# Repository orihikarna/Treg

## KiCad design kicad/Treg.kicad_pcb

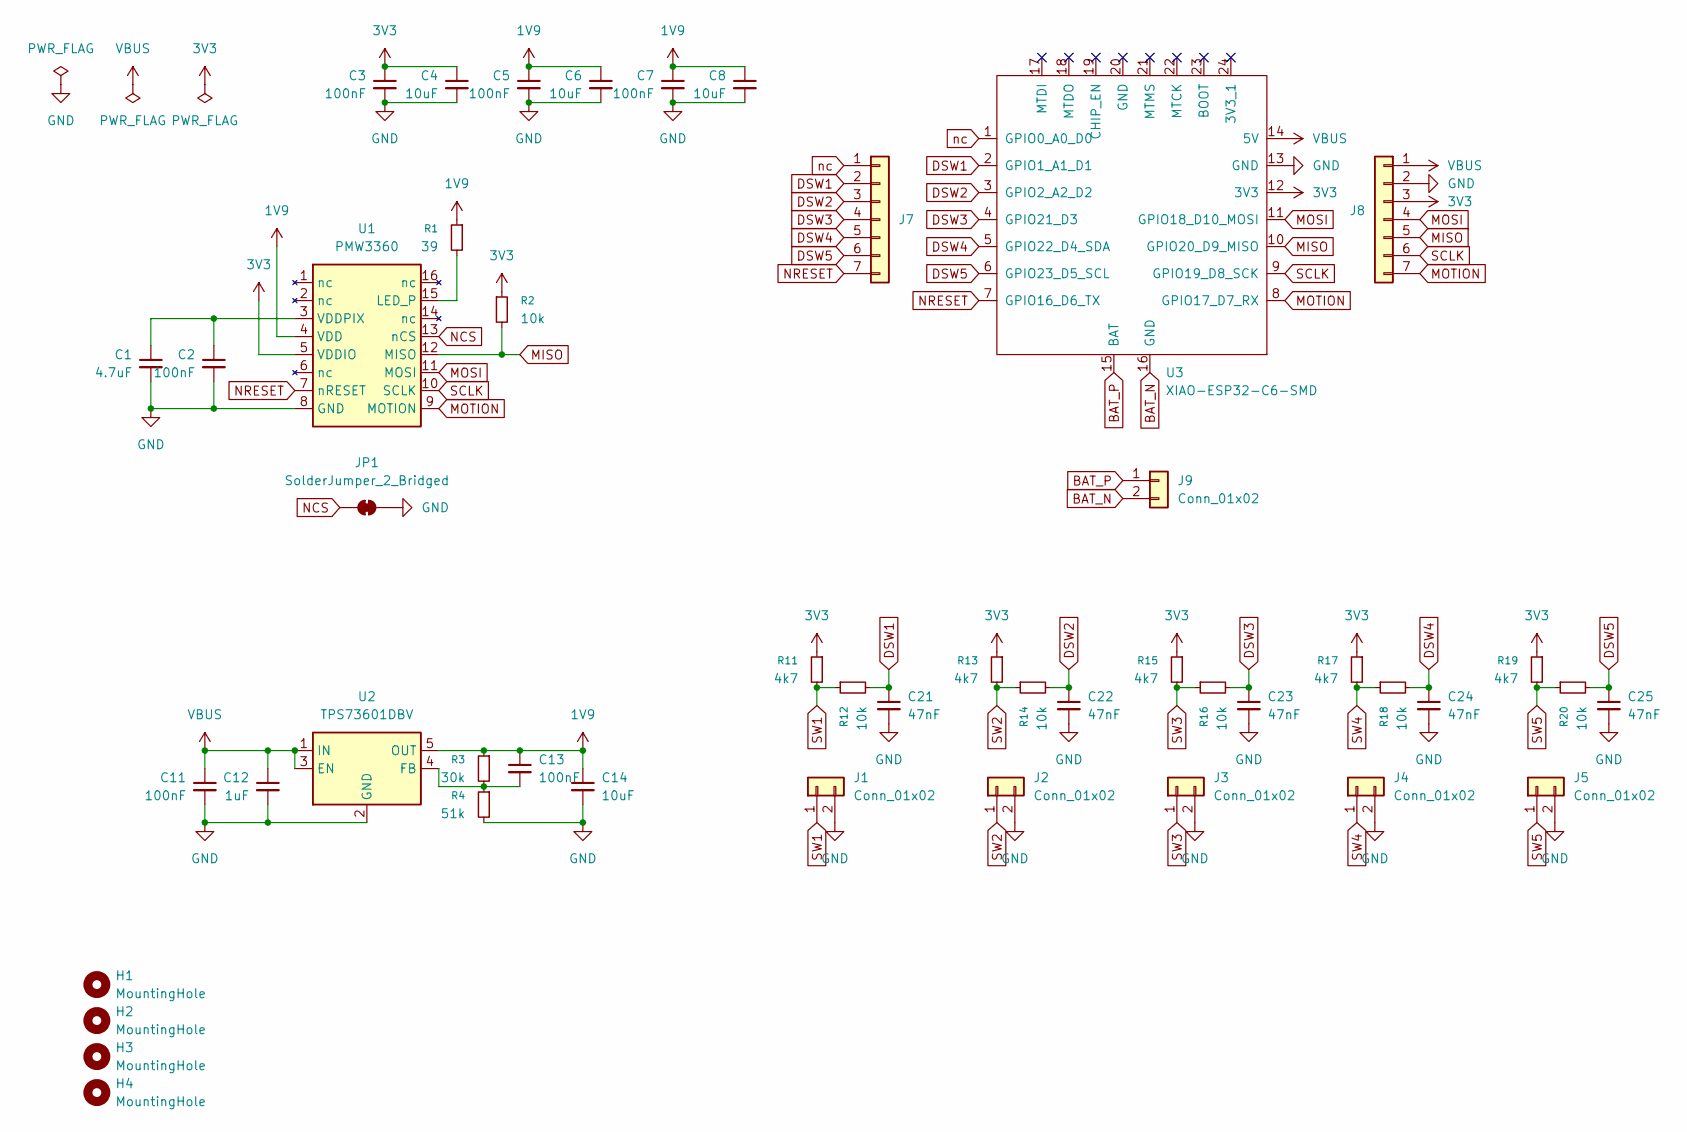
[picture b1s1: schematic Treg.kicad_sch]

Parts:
C1: 4.7uF; C_0603_1608Metric
C2, C3, C5, C7, C11, C13: 100nF; C_0603_1608Metric
C4, C6, C8, C14: 10uF; C_0603_1608Metric
C12: 1uF; C_0603_1608Metric
C21, C22, C23, C24, C25: 47nF; C_0603_1608Metric
H1, H2, H3, H4: MountingHole; MountingHole_2.2mm_M2
J1, J2, J3, J4, J5: Conn_01x02; PinHeader_1x02_P2.54mm_Vertical
J7, J8: Conn_01x07; PinHeader_1x07_P2.54mm_Vertical
J9: Conn_01x02; BatJumper
JP1: SolderJumper_2_Bridged; SolderJumper-2_P1.3mm_Bridged_RoundedPad1.0x1.5mm
R1: 39; R_0603_1608Metric_Pad0.98x0.95mm_HandSolder
R2, R12, R14, R16, R18, R20: 10k; R_0603_1608Metric
R3: 30k; R_0603_1608Metric
R4: 51k; R_0603_1608Metric
R11, R13, R15, R17, R19: 4k7; R_0603_1608Metric
U1: PMW3360
U2: TPS73601DBV; TSOT-23-5
U3: XIAO-ESP32-C6-SMD; XIAO-ESP32C6-SMD

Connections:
1V9: C5.1, C6.1, C7.1, C8.1, C13.1, C14.1, R1.1, R3.1, U1.4 (VDD), U2.5 (OUT)
3V3: C3.1, C4.1, J8.3, R2.1, R11.1, R13.1, R15.1, R17.1, R19.1, U1.5 (VDDIO), U3.12 (3V3)
BAT_N: J9.2, U3.16 (GND)
BAT_P: J9.1, U3.15 (BAT)
DSW1: C21.1, J7.2, R12.2, U3.2 (GPIO1_A1_D1)
DSW2: C22.1, J7.3, R14.2, U3.3 (GPIO2_A2_D2)
DSW3: C23.1, J7.4, R16.2, U3.4 (GPIO21_D3)
DSW4: C24.1, J7.5, R18.2, U3.5 (GPIO22_D4_SDA)
DSW5: C25.1, J7.6, R20.2, U3.6 (GPIO23_D5_SCL)
GND: C1.2, C2.2, C3.2, C4.2, C5.2, C6.2, C7.2, C8.2, C11.2, C12.2, C14.2, C21.2, C22.2, C23.2, C24.2, C25.2, J1.2, J2.2, J3.2, J4.2, J5.2, J8.2, JP1.2 (B), R4.2, U1.8 (GND), U2.2 (GND), U3.13 (GND)
MISO: J8.5, R2.2, U1.12 (MISO), U3.10 (GPIO20_D9_MISO)
MOSI: J8.4, U1.11 (MOSI), U3.11 (GPIO18_D10_MOSI)
MOTION: J8.7, U1.9 (MOTION), U3.8 (GPIO17_D7_RX)
NCS: JP1.1 (A), U1.13 (nCS)
NRESET: J7.7, U1.7 (nRESET), U3.7 (GPIO16_D6_TX)
unnamed: R1.2, U1.15 (LED_P)
unnamed: C1.1, C2.1, U1.3 (VDDPIX)
unnamed: C13.2, R3.2, R4.1, U2.4 (FB)
SCLK: J8.6, U1.10 (SCLK), U3.9 (GPIO19_D8_SCK)
SW1: J1.1, R11.2, R12.1
SW2: J2.1, R13.2, R14.1
SW3: J3.1, R15.2, R16.1
SW4: J4.1, R17.2, R18.1
SW5: J5.1, R19.2, R20.1
VBUS: C11.1, C12.1, J8.1, U2.1 (IN), U2.3 (EN), U3.14 (5V)
nc: J7.1, U3.1 (GPIO0_A0_D0)

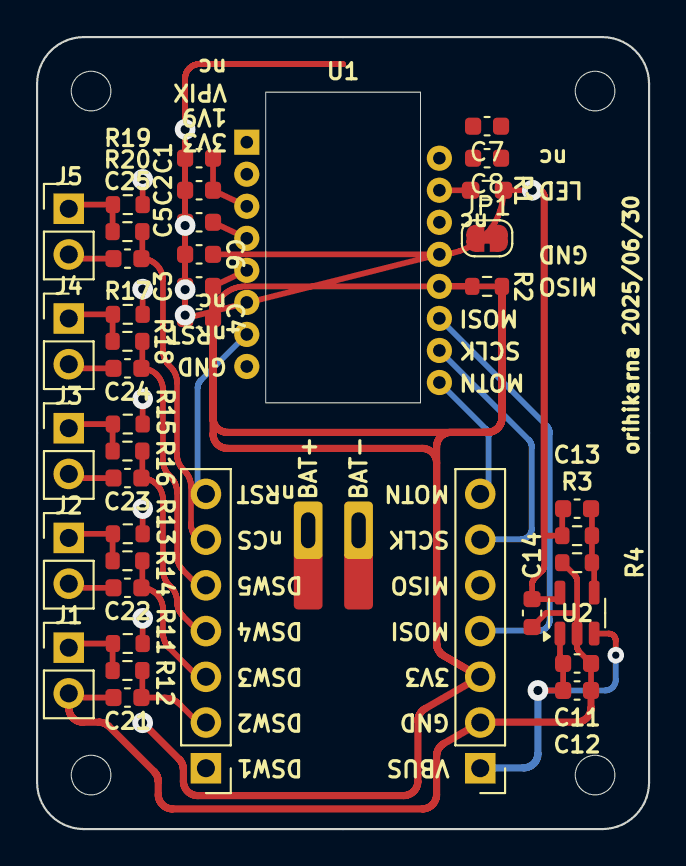
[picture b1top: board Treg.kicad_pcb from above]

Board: 4 copper layers, 34.0 x 44.0 mm, 47 parts (1 on the bottom side), 26 nets.

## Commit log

2025-02-06 add scad files
2025-02-06 add shell
2025-02-06 add vtk project
2025-02-07 try itk fast marching
2025-02-08 tr itk fast marching
2025-02-08 distance func to track egg
2025-02-08 fixed scaling
2025-02-09 offset distance, set outside points
2025-02-09 distance to the edge
2025-02-10 add impl note
2025-02-10 separated files
2025-02-10 separated files further
2025-02-10 remove util.h
2025-02-10 calc ridge
2025-02-12 distance to ridge
2025-02-12 fix size
2025-02-12 prep rendering
2025-02-13 fix params
2025-02-14 add test print model
2025-02-14 adj params
2025-02-22 adjust size
2025-02-26 elliptic egg
2025-02-26 tilt and resize egg shape
2025-03-01 no.4
2025-03-02 no.5
2025-03-02 no.6
2025-03-07 adding button hole
2025-03-09 [wip] tilt egg
2025-03-09 move orig
2025-03-09 fix hole size and origin
2025-03-09 add button
2025-03-16 switch hole
2025-03-22 no.7
2025-03-23 define btn ear params
2025-03-28 add holes for ball removal
2025-03-28 adjust shell size
2025-03-28 adjust switch pcb size
2025-03-28 adjust screw hole diameter
2025-03-28 define clearance
2025-03-28 sloped btn ear
2025-03-28 add base
2025-03-29 no.8
2025-03-29 update c++
2025-03-29 flip ball pos
2025-03-29 adjust sw pcb size
2025-03-29 adjust screw hole size
2025-03-29 switch hole triangle roof
2025-03-30 button shape
2025-04-04 pcba hole
2025-04-04 button support
2025-04-05 support ball hole
2025-04-05 extend suport hole
2025-04-06 no.9 add thicken bottom
2025-04-07 no.10
2025-04-08 no.10-1
2025-04-08 no.10-2
2025-04-09 no.10-3
2025-04-09 no.10-4
2025-04-13 adjust support ball pos
2025-04-13 add switch wire hole
2025-04-13 clan
2025-04-13 no.11
2025-04-19 wip hinge
2025-04-19 add hole
2025-04-26 clean
2025-04-26 no.12 test
2025-04-27 separated
2025-04-27 change ball removal hole
2025-04-27 switch wire hole
2025-04-27 pin hole ditch
2025-04-27 no.13
2025-04-29 adjust slit pos
2025-05-01 add pcb
2025-05-01 no.15
2025-05-02 sloped pcba hole
2025-05-03 adjust layout
2025-05-04 triangular roof
2025-05-07 add python
2025-05-08 placing mods
2025-05-10 add footprints, bat
2025-05-11 place mods
2025-05-11 silk
2025-05-11 bat silk
2025-05-14 replace parts with non-hand-solder, adjust refs
2025-05-18 start wiring
2025-05-21 wire sw, ldo
2025-05-22 wire sw
2025-05-24 wiring gnd
2025-05-24 wiring ldo
2025-05-24 wiring almost done
2025-05-25 add caps, jp
2025-05-25 add C9
2025-05-25 rewiring sw, pmw
2025-05-25 wiring caps
2025-06-08 removed jp1
2025-06-15 wiring pwr
2025-06-21 wired all
2025-07-06 fix ldo wiring
2025-08-11 adjust wiring
2025-08-11 add zones
2025-08-11 cleaning wire
2025-08-16 add gnd vias
2025-08-16 todo
2025-08-16 add rule area
2025-08-16 fix rule area
2025-08-16 adjusting foot prints
